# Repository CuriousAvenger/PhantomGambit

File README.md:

# PhantomGambit
The Phantom Gambit is a smart chessboard that can move pieces on its own, letting you play chess hands-free. Using hidden magnets and a tiny computer, it smoothly glides pieces across the board as if by magic. Whether you're playing against a friend or an AI, the board brings a unique, almost lifelike experience to the game—it's like having an invisible opponent right there with you.

# BOM
https://docs.google.com/spreadsheets/d/1c5iFp7m9ee2j3huvuUchwQKQikQjN13B6d_CP39HWaw/edit?usp=sharing

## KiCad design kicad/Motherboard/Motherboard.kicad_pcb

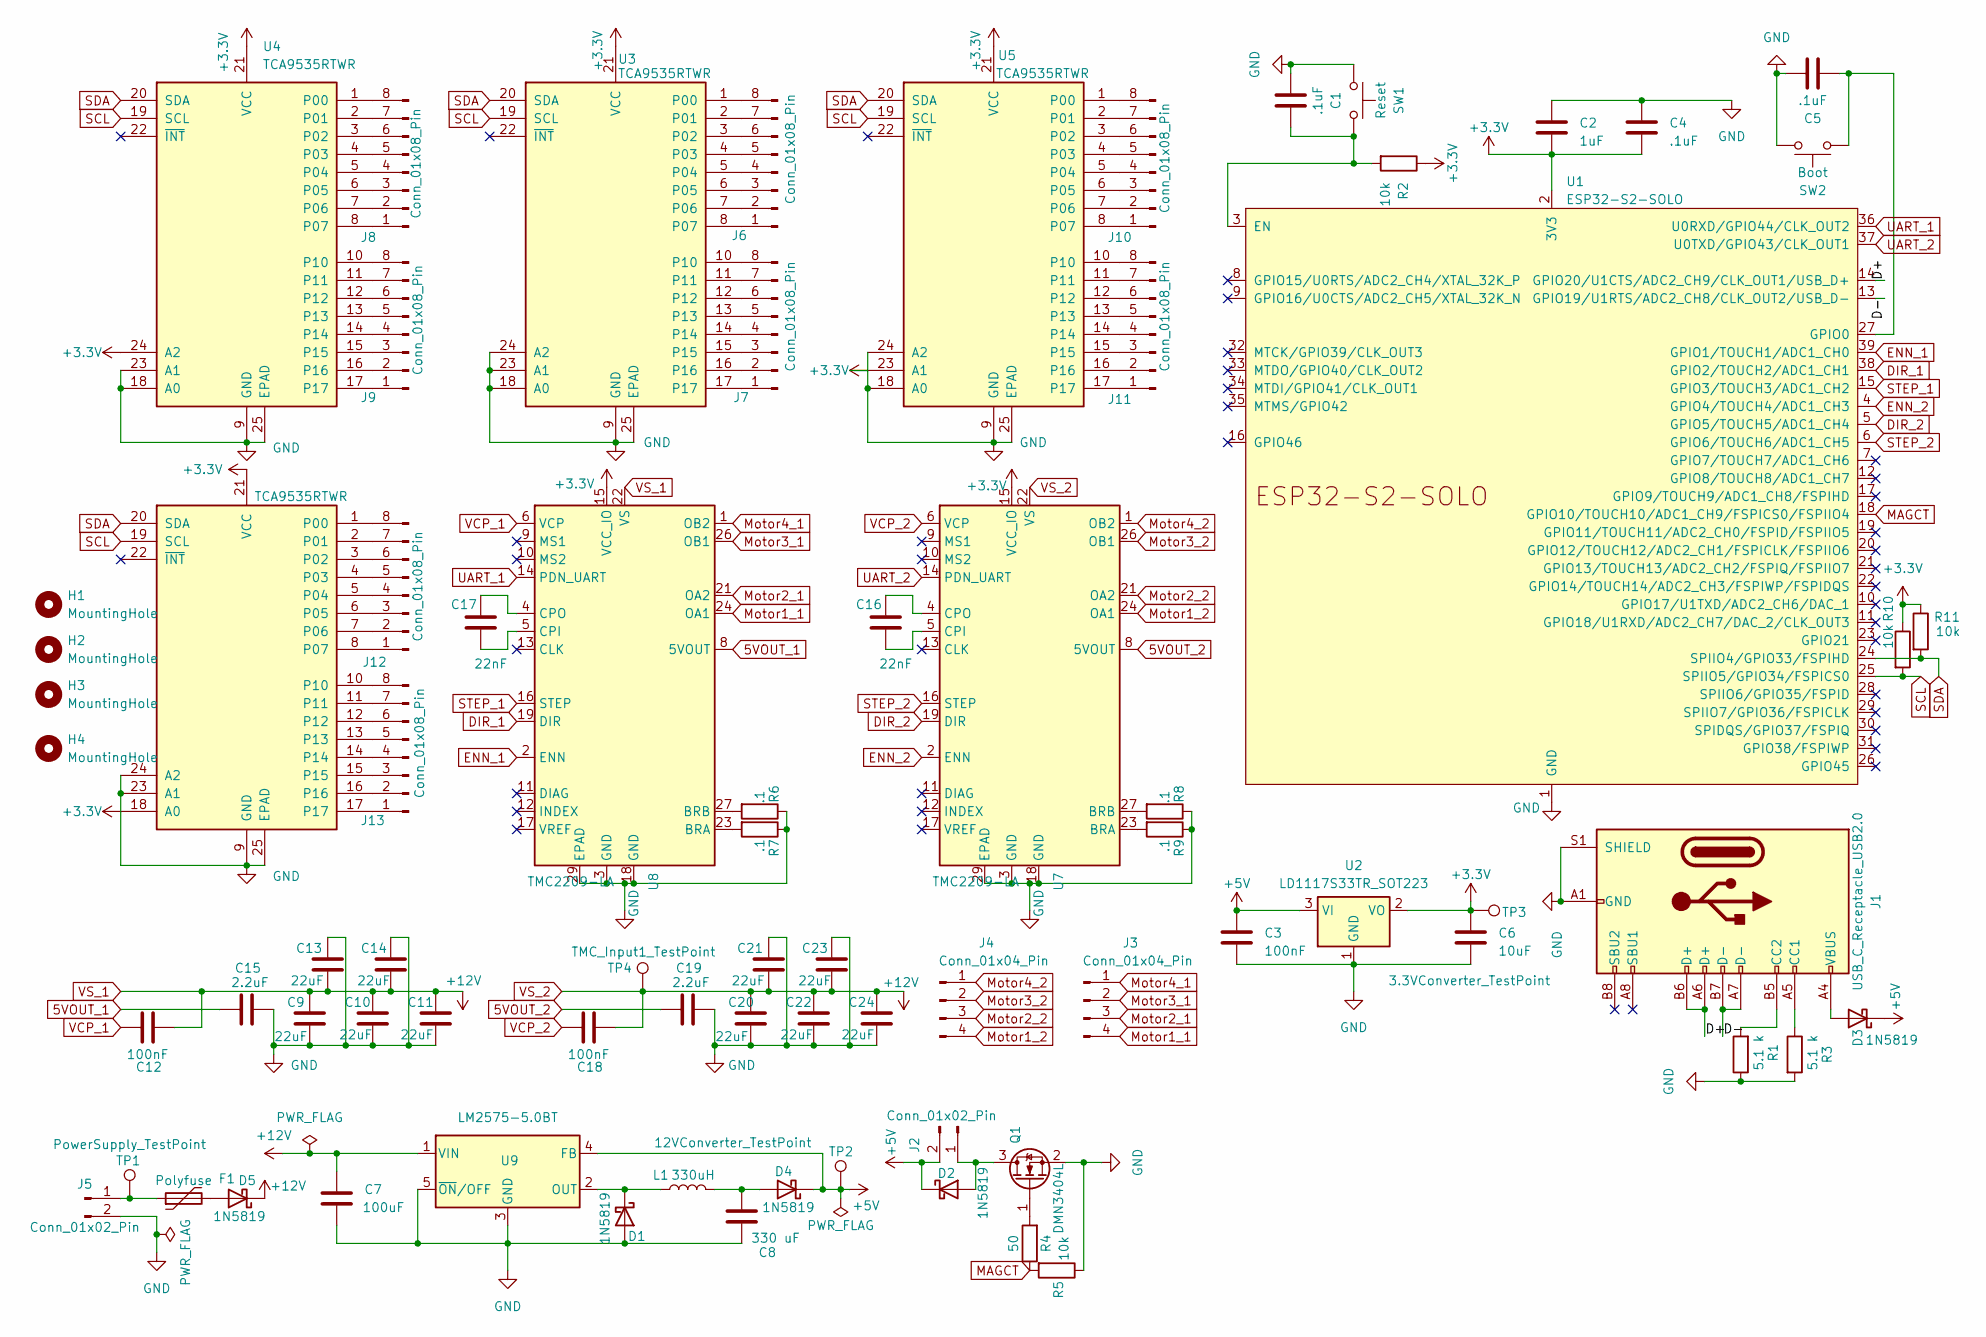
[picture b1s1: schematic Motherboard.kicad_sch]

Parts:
C1, C4, C5: .1uF; C_0805_2012Metric_Pad1.18x1.45mm_HandSolder
C2: 1uF; C_0805_2012Metric_Pad1.18x1.45mm_HandSolder
C3, C12, C18: 100nF; C_0805_2012Metric_Pad1.18x1.45mm_HandSolder
C6: 10uF; C_0805_2012Metric_Pad1.18x1.45mm_HandSolder
C7: 100uF; C_1210_3225Metric_Pad1.33x2.70mm_HandSolder
C8: 330 uF; C_1210_3225Metric_Pad1.33x2.70mm_HandSolder
C9, C10, C11, C13, C14, C20, C21, C22, C23, C24: 22uF; C_0805_2012Metric_Pad1.18x1.45mm_HandSolder
C15, C19: 2.2uF; C_0805_2012Metric_Pad1.18x1.45mm_HandSolder
C16, C17: 22nF; C_0805_2012Metric_Pad1.18x1.45mm_HandSolder
D1, D2, D3, D4, D5: 1N5819; D_DO-41_SOD81_P5.08mm_Vertical_AnodeUp
F1: Polyfuse; Fuse_2920_7451Metric_Pad2.10x5.45mm_HandSolder
H1, H2, H3, H4: MountingHole
J1: USB_C_Receptacle_USB2.0; USB_C_Receptacle_HRO_TYPE-C-31-M-12
J2, J5: Conn_01x02_Pin; PinHeader_1x02_P2.54mm_Vertical
J3, J4: Conn_01x04_Pin; PinHeader_1x04_P2.54mm_Vertical
J6, J7, J8, J9, J10, J11, J12, J13: Conn_01x08_Pin; PinHeader_1x08_P2.54mm_Vertical
L1: 330uH; L_1008_2520Metric_Pad1.43x2.20mm_HandSolder
Q1: DMN3404L; SOT-23
R1, R3: 5.1 k; R_0805_2012Metric_Pad1.20x1.40mm_HandSolder
R2, R5, R10, R11: 10k; R_0805_2012Metric_Pad1.20x1.40mm_HandSolder
R4: 50; R_0805_2012Metric_Pad1.20x1.40mm_HandSolder
R6, R7, R8, R9: .1; R_0805_2012Metric_Pad1.20x1.40mm_HandSolder
SW1: Reset; SW_Push_SPST_NO_Alps_SKRK
SW2: Boot; SW_Push_SPST_NO_Alps_SKRK
TP1: PowerSupply_TestPoint; TestPoint_Pad_1.5x1.5mm
TP2: 12VConverter_TestPoint; TestPoint_Pad_1.5x1.5mm
TP3: 3.3VConverter_TestPoint; TestPoint_Pad_1.5x1.5mm
TP4: TMC_Input1_TestPoint; TestPoint_Pad_1.5x1.5mm
U1: ESP32-S2-SOLO
U2: LD1117S33TR_SOT223; SOT-223-3_TabPin2
U3, U4, U5, U6: TCA9535RTWR; WQFN-24-1EP_4x4mm_P0.5mm_EP2.45x2.45mm
U7, U8: TMC2209-LA; TQFN-28-1EP_5x5mm_P0.5mm_EP3.25x3.25mm_ThermalVias
U9: LM2575-5.0BT; TO-220-5_Vertical

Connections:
5VOUT_1: C15.2, U8.8 (5VOUT)
5VOUT_2: C19.2, U7.8 (5VOUT)
+5V: C3.1, D2.1 (K), D3.1 (K), D4.1 (K), J2.2, TP2.1, U2.3 (VI), U9.4 (FB)
/D+: J1.A6 (D+), J1.B6 (D+), U1.14 (GPIO20/U1CTS/ADC2_CH9/CLK_OUT1/USB_D+)
/D-: J1.A7 (D-), J1.B7 (D-), U1.13 (GPIO19/U1RTS/ADC2_CH8/CLK_OUT2/USB_D-)
DIR_1: U1.38 (GPIO2/TOUCH2/ADC1_CH1), U8.19 (DIR)
DIR_2: U1.5 (GPIO5/TOUCH5/ADC1_CH4), U7.19 (DIR)
ENN_1: U1.39 (GPIO1/TOUCH1/ADC1_CH0), U8.2 (ENN)
ENN_2: U1.4 (GPIO4/TOUCH4/ADC1_CH3), U7.2 (ENN)
MAGCT: R4.1, R5.2, U1.18 (GPIO10/TOUCH10/ADC1_CH9/FSPICS0/FSPIIO4)
Motor1_1: J3.4, U8.24 (OA1)
Motor1_2: J4.4, U7.24 (OA1)
Motor2_1: J3.3, U8.21 (OA2)
Motor2_2: J4.3, U7.21 (OA2)
Motor3_1: J3.2, U8.26 (OB1)
Motor3_2: J4.2, U7.26 (OB1)
Motor4_1: J3.1, U8.1 (OB2)
Motor4_2: J4.1, U7.1 (OB2)
unnamed: D1.1 (K), L1.1, U9.2 (OUT)
unnamed: D2.2 (A), J2.1, Q1.3 (D)
unnamed: D3.2 (A), J1.A4 (VBUS), J1.A9 (VBUS), J1.B4 (VBUS), J1.B9 (VBUS)
unnamed: C8.1, D4.2 (A), L1.2
unnamed: D5.2 (A), F1.2
unnamed: J1.A5 (CC1), R3.1
unnamed: J1.B5 (CC2), R1.2
unnamed: F1.1, J5.1, TP1.1
unnamed: J6.1, U3.8 (P07)
unnamed: J6.2, U3.7 (P06)
unnamed: J6.3, U3.6 (P05)
unnamed: J6.4, U3.5 (P04)
unnamed: J6.5, U3.4 (P03)
unnamed: J6.6, U3.3 (P02)
unnamed: J6.7, U3.2 (P01)
unnamed: J6.8, U3.1 (P00)
unnamed: J7.1, U3.17
unnamed: J7.2, U3.16
unnamed: J7.3, U3.15
unnamed: J7.4, U3.14
unnamed: J7.5, U3.13
unnamed: J7.6, U3.12
unnamed: J7.7, U3.11
unnamed: J7.8, U3.10
unnamed: J8.1, U4.8 (P07)
unnamed: J8.2, U4.7 (P06)
unnamed: J8.3, U4.6 (P05)
unnamed: J8.4, U4.5 (P04)
unnamed: J8.5, U4.4 (P03)
unnamed: J8.6, U4.3 (P02)
unnamed: J8.7, U4.2 (P01)
unnamed: J8.8, U4.1 (P00)
unnamed: J9.1, U4.17
unnamed: J9.2, U4.16
unnamed: J9.3, U4.15
unnamed: J9.4, U4.14
unnamed: J9.5, U4.13
unnamed: J9.6, U4.12
unnamed: J9.7, U4.11
unnamed: J9.8, U4.10
unnamed: J10.1, U5.8 (P07)
unnamed: J10.2, U5.7 (P06)
unnamed: J10.3, U5.6 (P05)
unnamed: J10.4, U5.5 (P04)
unnamed: J10.5, U5.4 (P03)
unnamed: J10.6, U5.3 (P02)
unnamed: J10.7, U5.2 (P01)
unnamed: J10.8, U5.1 (P00)
unnamed: J11.1, U5.17
unnamed: J11.2, U5.16
unnamed: J11.3, U5.15
unnamed: J11.4, U5.14
unnamed: J11.5, U5.13
unnamed: J11.6, U5.12
unnamed: J11.7, U5.11
unnamed: J11.8, U5.10
unnamed: J12.1, U6.8 (P07)
unnamed: J12.2, U6.7 (P06)
unnamed: J12.3, U6.6 (P05)
unnamed: J12.4, U6.5 (P04)
unnamed: J12.5, U6.4 (P03)
unnamed: J12.6, U6.3 (P02)
unnamed: J12.7, U6.2 (P01)
unnamed: J12.8, U6.1 (P00)
unnamed: J13.1, U6.17
unnamed: J13.2, U6.16
unnamed: J13.3, U6.15
unnamed: J13.4, U6.14
unnamed: J13.5, U6.13
unnamed: J13.6, U6.12
unnamed: J13.7, U6.11
unnamed: J13.8, U6.10
unnamed: Q1.1 (G), R4.2
unnamed: C1.2, R2.2, SW1.2, U1.3 (EN)
unnamed: C5.1, SW2.1, U1.27 (GPIO0)
unnamed: R9.2, U7.23 (BRA)
unnamed: R8.2, U7.27 (BRB)
unnamed: C16.2, U7.5 (CPI)
unnamed: C16.1, U7.4 (CPO)
unnamed: R7.2, U8.23 (BRA)
unnamed: R6.2, U8.27 (BRB)
unnamed: C17.2, U8.5 (CPI)
unnamed: C17.1, U8.4 (CPO)
SCL: R10.2, U1.25 (SPIIO5/GPIO34/FSPICS0), U3.19 (SCL), U4.19 (SCL), U5.19 (SCL), U6.19 (SCL)
SDA: R11.2, U1.24 (SPIIO4/GPIO33/FSPIHD), U3.20 (SDA), U4.20 (SDA), U5.20 (SDA), U6.20 (SDA)
STEP_1: U1.15 (GPIO3/TOUCH3/ADC1_CH2), U8.16 (STEP)
STEP_2: U1.6 (GPIO6/TOUCH6/ADC1_CH5), U7.16 (STEP)
UART_1: U1.36 (U0RXD/GPIO44/CLK_OUT2), U8.14 (PDN_UART)
UART_2: U1.37 (U0TXD/GPIO43/CLK_OUT1), U7.14 (PDN_UART)
VCP_1: C12.2, U8.6 (VCP)
VCP_2: C18.2, U7.6 (VCP)
VS_1: C7.1, C9.1, C10.1, C11.1, C12.1, C13.2, C14.2, C18.1, C20.1, C21.2, C22.1, C23.2, C24.1, D5.1 (K), TP4.1, U7.22 (VS), U7.28 (VS), U8.22 (VS), U8.28 (VS), U9.1 (VIN)

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
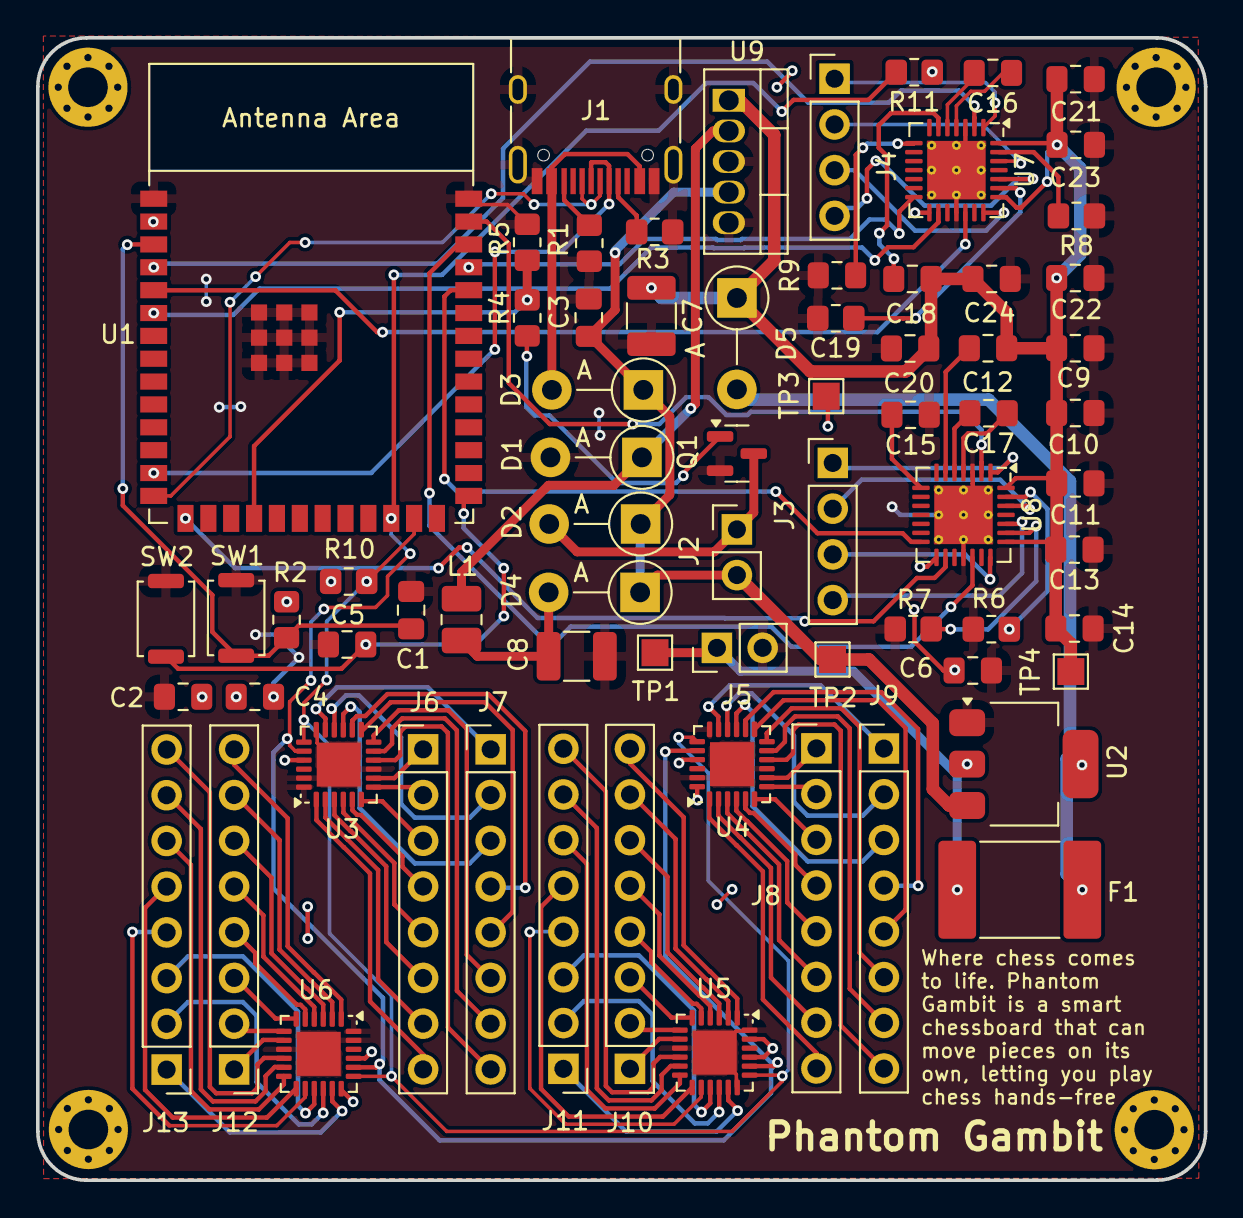
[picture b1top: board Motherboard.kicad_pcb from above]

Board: 2 copper layers, 64.9 x 63.5 mm, 71 parts (0 on the bottom side), 112 nets.

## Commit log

2024-10-23 added schematic
    schematic for the sensor board with halleffect sensors and the main motherboard with all the esp32 communication
2024-10-23 updated file system
2024-10-31 updated kicad
2024-10-31 Revert "Update README.md"
    This reverts commit da593d9038846133389d2f776026b393e5348709.
2024-10-31 Revert "updated file system"
    This reverts commit 047f54e2e744841bf1bb90de6ab8739a4d89a1a0.
2024-10-31 tcp2209
2024-11-01 tcp2209 all passives done
2024-11-01 fixed ground
2024-11-01 updated schematic
    schematic with updated tmc2208 driver and 16:1 mux passives.
2024-11-02 tmcs done
2024-11-02 updated schematic
2024-11-03 penultimate schematic
2024-11-03 Most of the layout done
2024-11-03 This commit actually has the changes
2024-11-04 Working on TMCs
2024-11-04 Didnt save yet
2024-11-04 TMC work
2024-11-04 idk what the fuck this is
2024-11-05 updated layout
2024-11-05 added stuff
2024-11-05 TMC in
2024-11-05 Test points added
2024-11-05 Need new render
2024-11-05 TestPoints named and layouts 1.5x1.5
2024-11-05 final schematic
2024-11-06 Final Schem done
2024-11-06 Latest board - need to update with new schematic
2024-11-06 Almost done - going to do a few more changes before I run the auto connector
    We may want to manually add them tho cus apple is going to look at it...
2024-11-06 huhu
2024-11-06 Gode
2024-11-06 finalized schematic
2024-11-06 re-render layout
2024-11-07 fixed schematic
2024-11-07 random sh
2024-11-07 schotty diode
2024-11-07 fixed layout
2024-11-07 Layout work
2024-11-07 finish pls sia
2024-11-07 Separated parts
2024-11-07 sai please
2024-11-07 I think we need to change something about the motor controllers
2024-11-07 bruh
2024-11-08 best layout
2024-11-08 penultimate layout
2024-11-08 good layout
2024-11-08 sai is bad at making connections
2024-11-08 try the switching parts
2024-11-08 Finished
2024-11-08 Done
2024-11-08 done agian
2024-11-08 corners
2024-11-08 job done mf
2024-11-08 change in capacitor
2024-11-08 Done and broke my computer
2024-11-08 Final sub
2024-11-08 finalized
2025-09-29 added new parts
